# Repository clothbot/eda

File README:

Unless otherwise stated, the files contained in this git repository are licensed under the GPL.

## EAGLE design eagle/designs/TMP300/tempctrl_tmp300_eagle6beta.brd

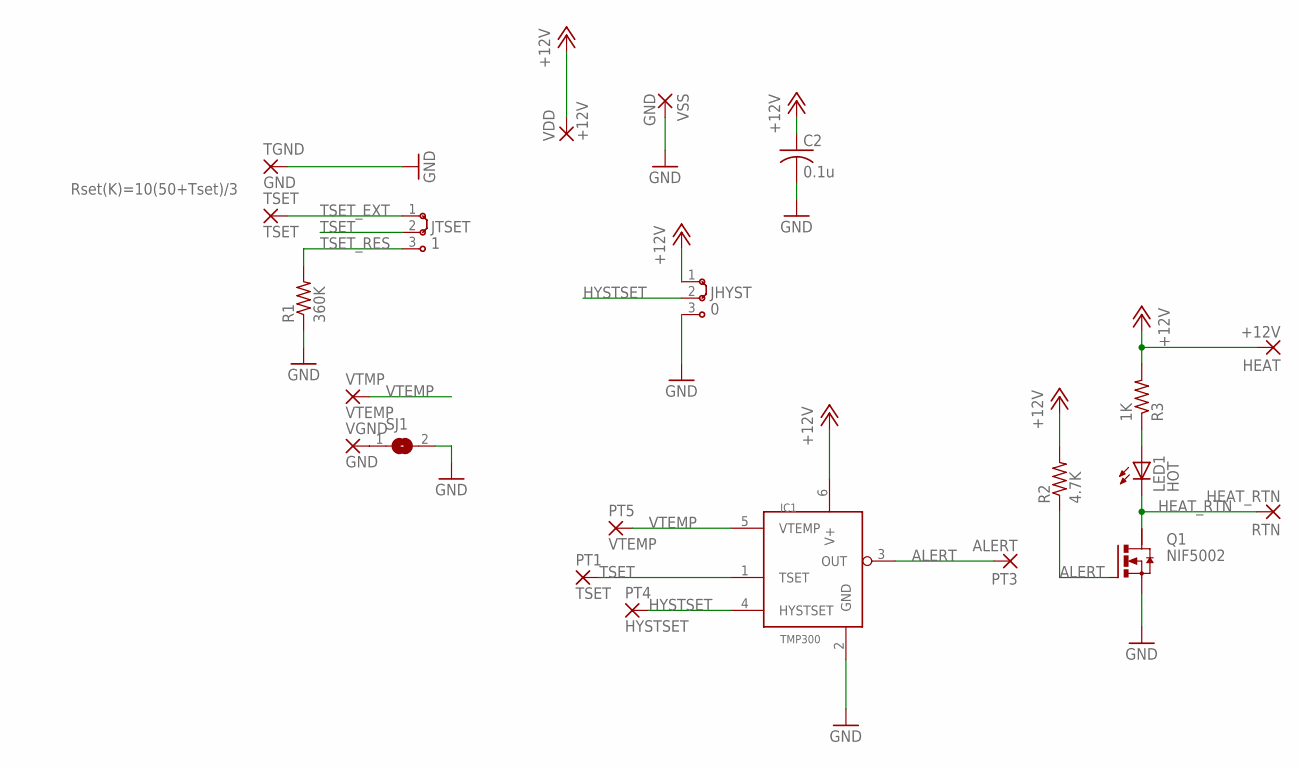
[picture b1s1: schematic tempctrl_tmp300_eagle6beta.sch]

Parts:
C2: 0.1u; C1206
HEAT: +12V; 2,54/1,1
IC1: TMP300; SOT23-6
JHYST: 0; 04C
JTSET: 1; 04C
LED1: HOT; LED-1206
PT1: TSET; 1,6/0,9
PT3: ALERT; 1,6/0,9
PT4: HYSTSET; 1,6/0,9
PT5: VTEMP; 1,6/0,9
Q1: NIF5002; SOT223
R1: 360K; R1206
R2: 4.7K; R1206
R3: 1K; R1206
RTN: HEAT_RTN; 2,54/1,1
SJ1: SJ
TGND: GND; 2,54/1,0
TSET: TSET; 2,54/1,0
VDD: +12V; 2,54/1,0
VGND: GND; 2,54/1,0
VSS: GND; 2,54/1,0
VTMP: VTEMP; 2,54/1,0

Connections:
+12V: C2.1, HEAT.1, IC1.6 (V+), JHYST.1, R2.2, R3.2, VDD.1
ALERT: IC1.3 (OUT), PT3.1, Q1.1 (G), R2.1
GND: C2.2, IC1.2 (GND), JHYST.3, Q1.3 (S), R1.1, SJ1.2, TGND.1, VSS.1
HEAT_RTN: LED1.C, Q1.2 (D), RTN.1
HYSTSET: IC1.4 (HYSTSET), JHYST.2, PT4.1
unnamed: SJ1.1, VGND.1
unnamed: LED1.A, R3.1
TSET: IC1.1 (TSET), JTSET.2, PT1.1
TSET_EXT: JTSET.1, TSET.1
TSET_RES: JTSET.3, R1.2
VTEMP: IC1.5 (VTEMP), PT5.1, VTMP.1

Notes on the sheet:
Rset(K)=10(50+Tset)/3

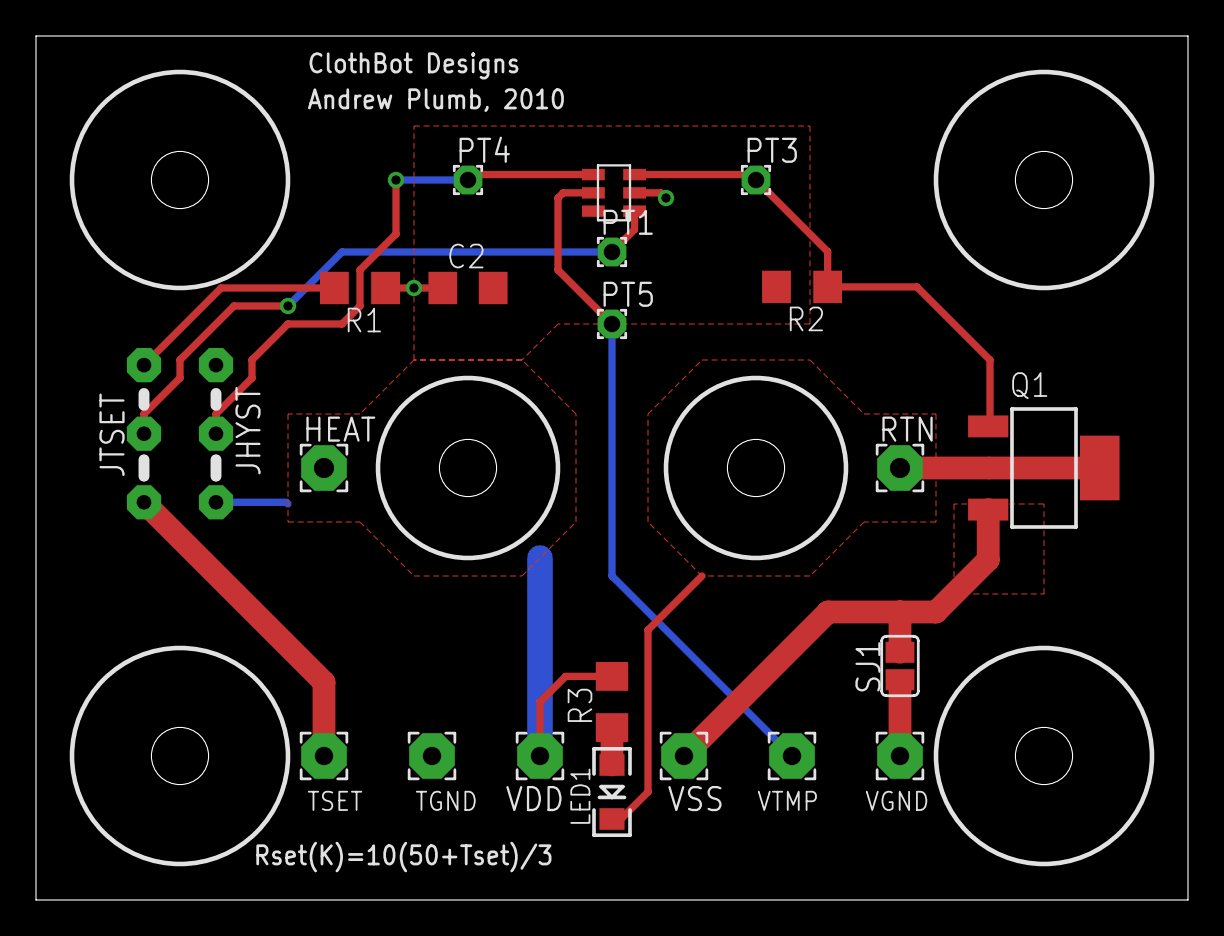
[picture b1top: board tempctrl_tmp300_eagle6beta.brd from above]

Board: 2 copper layers, 64.0 x 48.0 mm, 28 parts (0 on the bottom side), 11 nets.

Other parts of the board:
U$1, U$2, U$3, U$4, U$5, U$6: DRILL_0.1250

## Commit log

2010-05-27 Initial add of existing eda-related files.
2010-05-27 added content to README
2010-06-08 Created openscad parameterized adns-2610 package model.
2010-06-09 Created Makefiles for CLI execution of OpenSCAD.
2010-06-14 Changed render_part to adns2610_render_part.
2010-06-14 Added some color to the rendered examples.
2010-06-14 Added prefix to pin_socket_render_part and created adns2610_placeAtPinLocations operator module.
2010-06-14 Fixed non-manifold issue with pin_sockets abutted at single points instead of overlapped.
2010-06-14 Changed "include" to "use".
2010-06-14 Added adns2610_placeAtPin operator and simple socketed circuit work in progress.
2010-06-14 Added color-coded VDD and GND connections.
2010-06-14 Added REFA connect to pin 8 and adjusted pin locations.
2010-06-15 Added tdk ceramic resonator and worked on more of the adns-2610 test circuit.
2010-06-15 Fixed up union ops and origin of inverse socket dev circuit.
2010-06-20 Added experimental DXF slice generation code using openscad projection operator.
2010-06-24 Initial checkin of stl2pov-2.4.3 to manage changes needed to get it compiling on Mac OS X.
2010-06-24 Changed include and ifdef syntax.
2010-06-24 Initial add of dxflib-2.2.0.0-1.src for personal GPL-licensed software development stuff.
2010-06-24 Moving stl2pov-2.4.3 to a generic stl2pov subdirectory name.
2010-06-24 Deleting old stl2pov-2.4.3 named subdirectory.
2010-06-25 Added operations slicer and shell functions.
2010-06-25 Broke out slicer and added shelling operations.
2010-06-25 Added fill_mask creation.
2010-06-25 Added jobpool hooks to try running slicing, shelling and fill_masking in parallel. It works!
2010-06-26 Added slicer_slab and (broken) import_stl slicer.
2010-06-26 Added slicer_slab variant.
2010-06-26 Added test for breaking import_stl.
2010-06-27 Removed redundant slicer code.
2010-06-27 Removed dummy wrapper module; use import_stl directly even though it's currently broken.
2010-06-27 New fill operations (wip) and test stl with null faces removed.
2010-06-27 Pointing at stl with null faces removed.
2010-06-28 Simplified fill centering code.
2010-06-28 Clean .jobpool files.
2010-06-28 Added linear fill example and animation test.
2010-06-28 Cleaned up fill code.
2010-06-28 Created makerbot.scad parameters file and quantized slice and draw examples. work in progress.
2010-07-02 Added test to exercise projection() with/out import_stl.
2010-07-02 Split off stl generation to separate Makefile.STL.
2010-07-02 Fixed case of STL.
2010-07-02 Fixed typo in rule.
2010-07-02 Added diff_import_stl testcase.
2010-07-02 forgot to add diff_import_stl to make all.
2010-07-02 Added examples of fixed internal winding direction and meshlab fixed normals.
2010-07-02 Added convexity=2.
2010-08-03 Framework for board export.
2010-08-03 More board work.
2010-08-08 Work in progress on board functions.
2010-08-09 UL_PAD wip.
2010-08-23 Initial add of ohmite/MetalMite.scad model of chassis mount resistors used in Plastruder Mk5 heater.
2011-04-19 Commiting some old changes and a shell_spherical() operator module.
2011-08-24 Added color().
2011-08-24 Initial commit.
2011-08-24 Initial add.
2011-08-24 Added clean.
2011-11-04 Initial commit of eagle5 vs eagle6 (XML) example.
2011-11-04 PDF version of schematic and board for reference.
2011-11-04 Added jumper instance.
2011-11-04 Deleted wire segment.
2011-11-04 Moved ground symbol and connected wire.
2011-11-04 Moved jumper into position and wired up ground connection.
2011-11-04 Automatically modified board after jumper added and wired up on schematic side.
2011-11-04 Moved jumper near final position; rotate part seems broken.
2011-11-04 Drew wire.
2011-11-04 Manually added rot="R90" for component and ripped previous wire.
2011-11-04 Finished up routing.
2011-11-04 Modified rectangle dimensions.
2011-11-04 Shifted jumper over to allow for wired connection to thru-hole terminal.
2011-11-04 Ignore intermediate files.
2011-11-07 Adding eagle.dtd for reference - copied from 5.91.1 beta; no changes have been made as per CC-By-ND license.
2011-11-07 XSL Transform to generate OpenSCAD directly from an Eagle board file. WIP.
2011-11-07 Work in progress and created Makefile.
2011-11-07 Added pad.
2011-11-07 Added clean
2011-11-08 Breaking out scad wire module.
2011-11-08 Simplified wire call and added text-scad.
2011-11-08 Changed text template to use scad code.
2011-11-08 Added eagle_circle.
2011-11-08 Added rectangle.
2011-11-08 Added wire ends.
2011-11-08 Added smd and pad hole control.
2011-11-08 Added variable-controlled rendering of individual layers and holes (yes,no,only).
2011-11-09 Added polygon and via.
2011-11-09 Fixed shell_sphere trig bug.
2011-11-09 Package and signal wrapping WIP.
2011-11-09 More signal wip. cleaning up name character mapping.
2011-11-09 Prefixing package instances and replacing flat signal instantiation with module-based wrapper.
2011-11-09 Refactored board module.
2011-11-09 Breaking out render3d code.
2011-11-09 Added holes and more render3d action. WIP.
2011-11-10 Added rank parameter.
2011-11-10 Setting fill=false.
2011-11-10 Wrapping signal() and package() in wrapper modules with proper name lookup mappings.
2011-11-10 Wrapping layer info in array with lookup function.
2011-11-10 Testing layer_lookup.
2011-11-10 Deleting unused code and adding more verbose Ignore comments.
2011-11-10 Created ulp subdirectory.
2011-11-14 Working on polygon outline code.
2011-11-14 polygon_outline code works!
2011-11-14 Added "extend" hooks for future signal isolation hooks.
2011-11-16 Added rank logic.
2011-11-16 Grouping by layer. WIP.
2011-11-16 refactoring board calls
2011-11-16 Cleaning up layer refactoring. Still WIP, but still works.
